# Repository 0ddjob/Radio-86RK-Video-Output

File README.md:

# Radio 86RK Video Output
The РАДИО-86РК was a Soviet-era homebrew/DIY computer based on their clone of the Intel 8080, the КР580ВМ80А.<br>
[Sergey Kiselev](https://github.com/skiselev) has [made a very nice modern recreation](https://github.com/skiselev/radio-86rk) that, importantly, outputs a "composite" video signal.<br>

Yes yes, "composite" means colour/luma+chroma but the machine outputs a luma/B&W-only video signal ... but you know what I mean ... the yellow RCA jack.<br>

The Intel 8275 (Soviet: КР580ВГ75) generates horizontal (HRTC) and vertical (VRTC) retrace signals which are combined with the character bitstream (character ROM to shift register) to produce the video output.  The image above shows one scanline with text - the negative-going pulses are HRTC & VRTC, the positive-going are character bits.<br>

The schematic below is a simplified version of Sergey's schematic highlighting how the video signal is generated.<br>

Sergey's implemention additionaly includes the reverse video (RVV) signal but this isn't implemented in all versions of the 86RK, so I'm ignoring (for now).<br>

The 86RK was serially produced by various factories in the Soviet Union resulting in machines such as the АЛЬФА-БК, ПАРТНЕР-01.01 and УМПК-Р.  These machines all output an RF-modulated video signal which is not convenient these days. <br>

To simplify conversion of these machines' video output I thought it might be worth implementing Sergey's video output stage as a discrete module that could be installed in these older machines.<br>

## Status: PARTIALLY TESTED
- 23-Nov-2024: initial design
- 25-Nov-2024: test PCBs ordered from PCBWAY
- 17-Dec-2024: [initial testing](https://youtu.be/Y1xS1cXXh0Q) on УМПК-Р but this machine has an underlying fault (DRAM?) so need to fix that first

## Initial Build
This is my dodgy "hand-made" version I whipped together when trying to get video out of a УМПК-Р, which convinced me that a proper module might be better for future use.<br>

## Versions
I've made two versions: one with an RCA phono jack for testing/troubleshooting a machine without modifying too much and a second with a pin header for installation into a machine.

### [RCA Jack](/RCA_output/)
Selected the "same sky" part RCJ-014 as the phono jack.  Kicad library & datasheet are incuded.<br>

### [PIN Header](/Pin_header_output/)

## Bill of materials
- 2 x 1kΩ resistor
- 1 x 1.5kΩ resistor
- 1 x 75Ω resistor
- 1 x 150Ω resistor
- 1 x 2N3904 transistor
- 1 x 47µF electrolytic capacitor (pitch 2.5mm)
- 1 x 22nF ceramic capacitor (pitch 2.5mm)
- 1 x M3 bolt/nut/washer/spacer (if required)

For RCA phono jack version:
- 1 x RCJ-014 (or similar) RCA phono jack
- 1 x 4-pin header (pitch 2.54mm)

For pin header version:
- 1 x 5-pin header (pitch 2.54mm)

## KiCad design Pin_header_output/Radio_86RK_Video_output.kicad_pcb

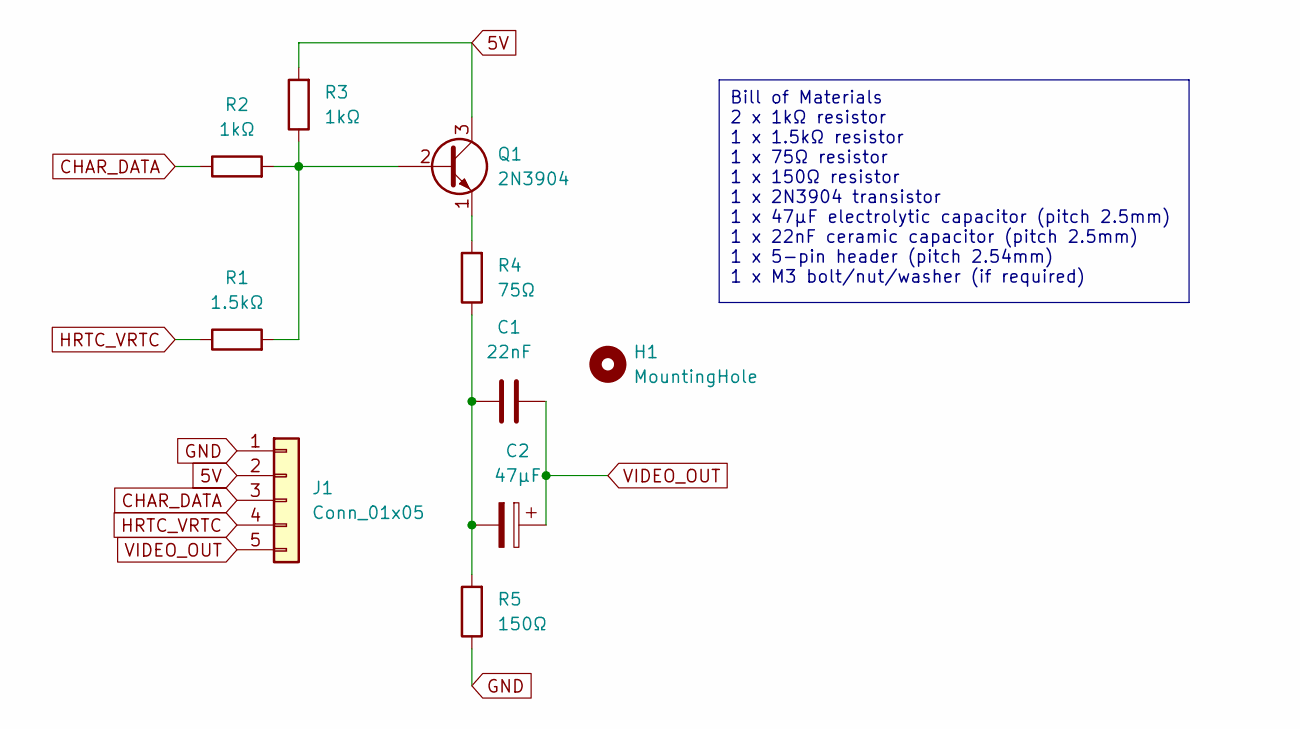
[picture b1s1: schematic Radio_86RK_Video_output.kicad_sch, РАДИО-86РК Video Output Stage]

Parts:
C1: 22nF; C_Disc_D3.8mm_W2.6mm_P2.50mm
C2: 47µF; CP_Radial_D5.0mm_P2.50mm
H1: MountingHole; MountingHole_3.2mm_M3
J1: Conn_01x05; PinHeader_1x05_P2.54mm_Vertical
Q1: 2N3904; TO-92_Inline
R1: 1.5kΩ; R_Axial_DIN0207_L6.3mm_D2.5mm_P2.54mm_Vertical
R2, R3: 1kΩ; R_Axial_DIN0207_L6.3mm_D2.5mm_P2.54mm_Vertical
R4: 75Ω; R_Axial_DIN0207_L6.3mm_D2.5mm_P2.54mm_Vertical
R5: 150Ω; R_Axial_DIN0207_L6.3mm_D2.5mm_P2.54mm_Vertical

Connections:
5V: J1.2, Q1.3 (C), R3.2
CHAR_DATA: J1.3, R2.1
GND: J1.1, R5.1
HRTC_VRTC: J1.4, R1.1
unnamed: C1.1, C2.2, R4.1, R5.2
unnamed: Q1.2 (B), R1.2, R2.2, R3.1
unnamed: Q1.1 (E), R4.2
VIDEO_OUT: C1.2, C2.1, J1.5

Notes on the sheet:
Bill of Materials 2 x 1kΩ resistor 1 x 1.5kΩ resistor 1 x 75Ω resistor 1 x 150Ω resistor 1 x 2N3904 transistor 1 x 47µF electrolytic capacitor (pitch 2.5mm) 1 x 22nF ceramic capacitor (pitch 2.5mm) 1 x 5-pin header (pitch 2.54mm) 1 x M3 bolt/nut/washer (if required)

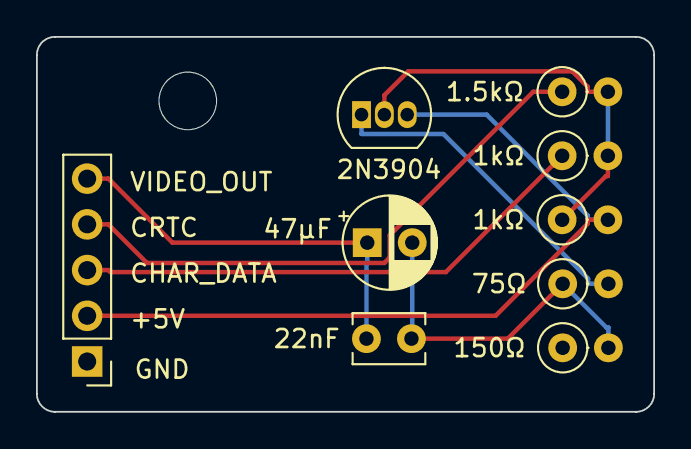
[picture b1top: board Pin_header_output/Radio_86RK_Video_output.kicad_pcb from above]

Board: 2 copper layers, 34.3 x 20.8 mm, 10 parts (0 on the bottom side), 8 nets.

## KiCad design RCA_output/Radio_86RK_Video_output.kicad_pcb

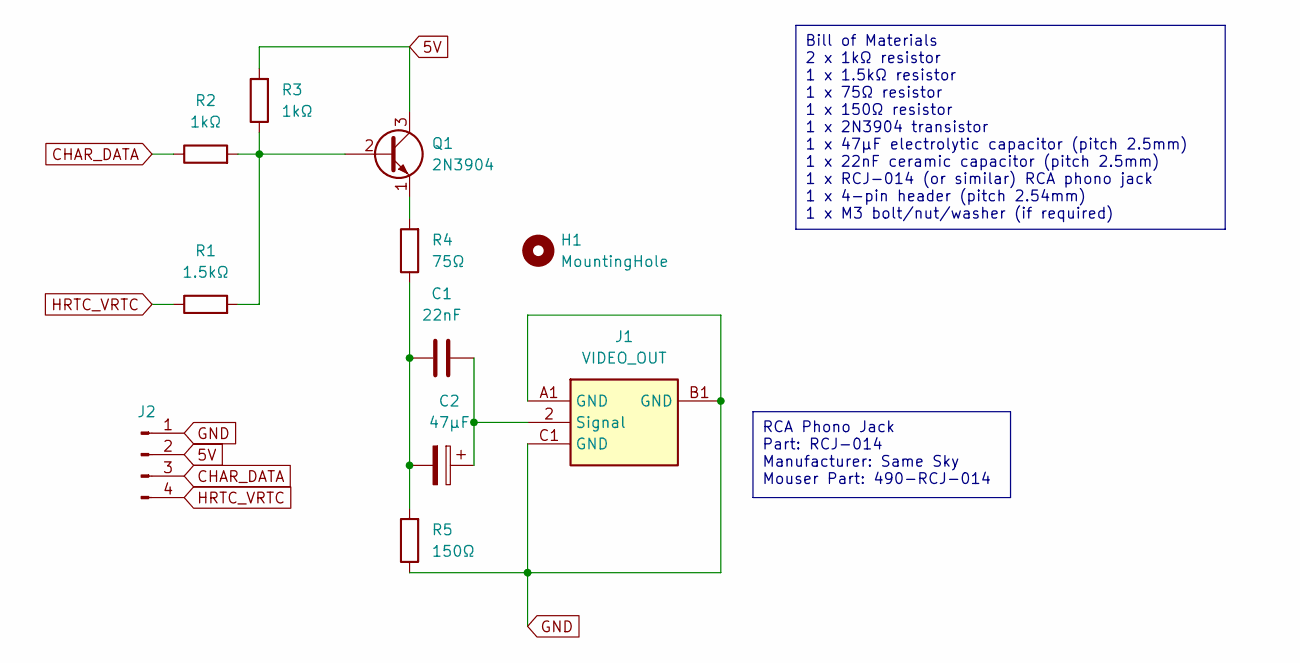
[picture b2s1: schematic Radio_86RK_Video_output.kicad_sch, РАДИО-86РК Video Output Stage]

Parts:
C1: 22nF; C_Disc_D3.8mm_W2.6mm_P2.50mm
C2: 47µF; CP_Radial_D5.0mm_P2.50mm
H1: MountingHole; MountingHole_3.2mm_M3
J1: VIDEO_OUT; RCJ014; Mouser Part Number 490-RCJ-014
J2: Conn_01x04_Pin; PinHeader_1x04_P2.54mm_Vertical
Q1: 2N3904; TO-92_Inline
R1: 1.5kΩ; R_Axial_DIN0207_L6.3mm_D2.5mm_P2.54mm_Vertical
R2, R3: 1kΩ; R_Axial_DIN0207_L6.3mm_D2.5mm_P2.54mm_Vertical
R4: 75Ω; R_Axial_DIN0207_L6.3mm_D2.5mm_P2.54mm_Vertical
R5: 150Ω; R_Axial_DIN0207_L6.3mm_D2.5mm_P2.54mm_Vertical

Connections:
5V: J2.2, Q1.3 (C), R3.2
CHAR_DATA: J2.3, R2.1
GND: J1.A1 (GND), J1.B1 (GND), J1.C1 (GND), J2.1, R5.1
HRTC_VRTC: J2.4, R1.1
unnamed: C1.1, C2.2, R4.1, R5.2
unnamed: C1.2, C2.1, J1.2 (Signal)
unnamed: Q1.2 (B), R1.2, R2.2, R3.1
unnamed: Q1.1 (E), R4.2

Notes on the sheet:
RCA Phono Jack Part: RCJ-014 Manufacturer: Same Sky Mouser Part: 490-RCJ-014
Bill of Materials 2 x 1kΩ resistor 1 x 1.5kΩ resistor 1 x 75Ω resistor 1 x 150Ω resistor 1 x 2N3904 transistor 1 x 47µF electrolytic capacitor (pitch 2.5mm) 1 x 22nF ceramic capacitor (pitch 2.5mm) 1 x RCJ-014 (or similar) RCA phono jack 1 x 4-pin header (pitch 2.54mm) 1 x M3 bolt/nut/washer (if re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

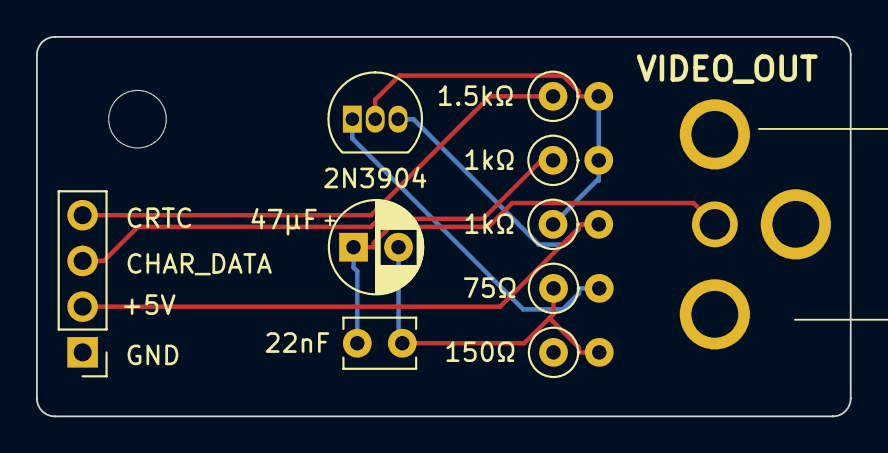
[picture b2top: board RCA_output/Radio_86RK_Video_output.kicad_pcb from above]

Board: 2 copper layers, 45.2 x 21.1 mm, 11 parts (0 on the bottom side), 8 nets.

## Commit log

2024-11-23 Initial
2024-11-23 Added mounting hole
2024-11-23 Changed HRTC_VRTC to CRTC
2024-11-24 Reorganise folders
